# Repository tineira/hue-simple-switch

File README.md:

# hue-simple-switch

Wi‑Fi wall switch for the **Seeed XIAO ESP32-C6**. Calls the Hue Bridge's local Clip v2 API (HTTPS). Not Zigbee.

GPIO channels (closed = pin to GND, `INPUT_PULLUP`):

| id | GPIO | default kind | label |
| --- | --- | --- | --- |
| `boot` | 9 | `momentary` | BOOT |
| `d0` | 0 | `maintained` | D0 |
| `d1` | 1 | `maintained` | D1 |
| `d2` | 2 | `maintained` | D2 |
| `d3` | 21 | none | D3 |
| `d4` | 22 | none | D4 |
| `d5` | 23 | none | D5 |

D3–D5 (GPIO 21–23) are channels since 0.5.0, so one board takes up to six wall switches or buttons on D0–D5, plus BOOT. None of D3–D5 is a strapping pin, and this firmware has no I2C on D4/D5. D6–D10 stay unused (D6 is the chip's serial TX at boot).

Since 0.3.0 the console picks each channel's kind (`maintained` = toggle switch, `momentary` = push button) and sends it in the config's `channels[]`; a pin it does not list does nothing. BOOT is always a push button. The default kinds above apply only to the old config payload (no `channels[]`), from a console that predates channel types; there D3–D5 do nothing, so an unwired pin never acts.

Each channel has recipes per event, derived by the console:

- Toggle switch, flip set (the lever sets on or off; no `flip` in `channels[]`): `on` (lever closes), `off` (lever opens, after the ~400 ms double-click window), `double_click` (opens and closes inside the window; runs `on` when there is no `double_click` recipe).
- Toggle switch, flip toggle (`"flip": "toggle"`, since 0.8.0; each flip toggles, the console sends `toggle` for both `on` and `off`): each flip posts `on` (lever closes) or `off` (lever opens) at once when there is no `double_click` recipe. With one, a flip either way waits ~400 ms: a second flip inside it is `double_click`, otherwise the first flip runs. No `on` fallback. A toggle that turned the lights off restarts the scene list. Boot, a config change or a change of the flip setting never toggles.
- Push button: `short` on release, at once when the channel has no `double_click` recipe; with one, a second press inside ~400 ms is `double_click` and an expired window is `short`. `hold` fires once at ~800 ms while pressed, only when the channel has a `hold` recipe.
- BOOT without a `hold` recipe: a 3 s press re-pairs with the Bridge. With one, the button never re-pairs (USB install only).
- A scene list (`recall_scene` with `targets[]`) cycles from the last scene the channel set (kept in NVS), wraps, skips scenes that answer 404, and starts over at the first scene after an `off` on the channel (in flip toggle mode, after a toggle that turned the target off).

The GPIO runs NVS → Bridge; it doesn't wait for Vercel. Since 0.5.0 the config is stored as one NVS blob per channel, so saving the largest config (seven channels with scene lists) needs only one channel's worth of free space; the first boot after the update converts the older single blob.

Wiring for up to six wall switches or buttons on D0–D5: [`docs/wiring-switches.svg`](docs/wiring-switches.svg). Wire only the inputs you use. The step-by-step build guide (what to buy, wiring one input at a time, what never to connect, and when you need the resistors) is at [hue.tineira.com/how-to](https://hue.tineira.com/how-to?product=simple#wire).

To power the switch from the mains inside a wall box, behind the existing switch, there is a carrier board design (KiCad) and a printable enclosure in [`hardware/`](hardware/README.md). It keeps the same pins and firmware. **Do not build it:** the current board has a known isolation defect, its order files are withdrawn and a revised board is pending. It is an uncertified, experimental mains design: read its safety notes.

> [!WARNING]
> **Safety.** Mains voltage can kill. The designs in this repository are uncertified and some are unproven, and the maintainer is not an electrical engineer. Rules and wire colors differ by country. Read the [Safety notice](https://hue.tineira.com/safety) before you build anything, and never connect any pin of a USB-powered build to anything that is or was on mains. Everything here is provided as is, without warranty, as the licenses say.

**BOOT** (GPIO9) and **RST** (CHIP_PU) are **buttons**, not LEDs. The board has two lights:

The orange LED's alphabet (firmware 0.2.7 and later) is below. Design history: [`docs/archive/specs/led-status.md`](docs/archive/specs/led-status.md).

| Light | Where | Driven by |
| --- | --- | --- |
| Orange (user, GPIO15 `LED_BUILTIN`) | Right side, next to RST | This firmware |
| Red (charging) | Next to the USB-C | The charger hardware; the sketch doesn't touch it |

### Orange LED (firmware)

One pattern at a time, top to bottom. When the step changes, the burst starts from zero. `LOW` on GPIO15 turns the orange on (active low).

| What you see | Meaning |
| --- | --- |
| Solid on | System error: the console task wasn't created, or the console answered 401. The 401 stays solid until a response with a code other than 401, or a new `HUESET token`. Wins even without Wi‑Fi. |
| Continuous blink ~2 Hz (250 ms on / 250 ms off) | No Wi‑Fi STA, or Improv scan. Even with a saved SSID. |
| 2 flashes and a pause | Wi‑Fi ok, no console (URL or token empty, or a `your-…` placeholder). |
| 3 flashes and a pause | Wi‑Fi and console, Hue not paired, or pairing in progress / timed out. Holding BOOT 3 s (re-pair) uses this pattern. |
| 4 flashes and a pause | Wi‑Fi, console and Hue, no recipes. |
| One short flash every ~3 s | Armed: one or more recipes. |

Burst (#2–#4): 100 ms on, 200 ms between flashes, 1400 ms pause. The armed flash lasts 80 ms and repeats every 3 s.

### Red LED (charging, not the sketch)

| What you see | Meaning |
| --- | --- |
| On for ~30 s when USB is plugged in without a battery | USB present; then it turns off. |
| Blinking | LiPo battery connected and charging over USB. |
| Off with USB and battery | Charge complete (or no charge cycle). |

Contract: `hue-switch-console/docs/definitions.md`, `docs/device-api.md` and `docs/usb-protocol.md`.

## Setup

1. Flash and provision from Chrome on [hue.tineira.com](https://hue.tineira.com) → Devices (USB). Improv saves the **2.4 GHz** network and `HUESET` stores the token (`hsw_…`) and url in NVS `console`. None of that is compiled in. For development, copy `config.example.h` to `config.h` (only `SERIAL_DEBUG`); `arduino-cli upload` doesn't erase NVS, so the network and token survive every flash.
2. The XIAO discovers the Bridge (mDNS `_hue._tcp`, NVS, `discovery.meethue.com`) and pairs the Hue key (three orange flashes → Bridge button). IP and key stay in NVS, not in `config.h`.
3. Register: `POST /api/device/register` with `product: "simple"`, MAC, `channels[]` and snapshot (lights/rooms/scenes). Poll: `GET /api/device/config?mac=&rev=&firmware=` at boot, then every `X-Poll-Sec` seconds from the console (clamped 30 s to 1 h; `204` = unchanged, keep NVS), once more right after a new `rev` is saved, and 1 h after a `401`. Without the header (older console): ~1 min without recipes, 1 h with some. With recipes, register (topology) at most hourly.
4. Arduino IDE 2.3.10: open `hue-simple-switch.ino`, board **XIAO_ESP32C6**.
5. Or arduino-cli: `arduino-cli compile --profile xiao-c6 .`

List lamps (diagnostics):

```
curl -k -H "hue-application-key: KEY" https://BRIDGE_IP/clip/v2/resource/light
```

`config.h` is not committed. Product onboarding = the USB installer on hue.tineira.com.

## Release

A push to `main` **is a release**. `.github/workflows/firmware.yml` builds the product image and uploads it to the console (hue.tineira.com) with this version's `CHANGELOG.md` entry as release notes. The console's USB installer then offers that build to every Simple plugged in over USB, and since 0.6.0 the owner can send it over Wi-Fi from the Switches page (below). The workflow also keeps the `usb-installer` GitHub Release as a download link. Pushes that change only docs or the board design (`*.md`, `docs/`, `hardware/`) do not run it, except `CHANGELOG.md`, which re-sends the notes. To skip any other push, put `[skip ci]` in its commit message.

- `FIRMWARE_VERSION` in `console.h` is the version the console shows. Bump it for any change a board should pick up, and add its entry to `CHANGELOG.md` in the same commit. A push without a bump re-sends the notes only (`409 version_exists` warning).
- `THIRD_PARTY.json` lists the open-source components linked into the image (the core, ESP-IDF, and every library pinned in `sketch.yaml`), with version, SPDX license and a link to the license at that version. CI sends it as the release `credits` for the console's Credits page, and fails if any `platform:` or `libraries:` entry in `sketch.yaml` is missing from it or has a different version (`scripts/check-credits.py`, run on every pull request too). Update it in the same commit as any core or library bump.
- Update over Wi-Fi (0.6.0+; wire: console `docs/device-api.md`, design history: console `docs/archive/specs/ota.md`): when the owner presses Update, the next poll's `200` carries `ota` (version, path, sha256, size). After the poll's connection is closed, the console task downloads `firmware.bin` from the console URL in NVS, writes it to the inactive app slot while hashing it, checks length and sha256, and restarts into it. It waits for the next poll while an input is pressed or a Hue call is queued or running. The new image confirms itself after its first `200`/`204` poll; a restart before that makes the bootloader go back to the old one, which reports `ota_error=boot`. A failure is reported once as `ota_error` and retried at most hourly (a download cut off by a power cut or restart counts, reported as `size` at the next boot, since 0.6.1) (`size`/`sha` from a bad image: not until reboot). NVS is never erased. Boards before 0.6.0 need one USB update first.
- Image layout and offsets: [`docs/firmware-artifacts.md`](docs/firmware-artifacts.md).
- The pipeline needs the `FIRMWARE_UPLOAD_TOKEN` secret in this repo. Setup and troubleshooting: the console repo's `README.md`, "Firmware release pipeline".

### Build and upload from a fork

A fork builds the same image on every push to its `main`, and can upload it to your own console instead of hue.tineira.com (self-hosting: the console repo's `docs/self-hosting.md`).

- **Build only (default).** With no `FIRMWARE_UPLOAD_TOKEN` secret, the workflow builds, skips the upload with a notice and stays green. The four installer parts are in the run's `usb-installer-simple` artifact and in the fork's `usb-installer` GitHub Release.
- **Upload to your console.** In the fork's **Settings → Secrets and variables → Actions**:
  1. Add the repository **variable** `CONSOLE_UPLOAD_URL` with your console's origin, for example `https://hue.example.com` (no path, no trailing slash). Without it, the upload goes to `https://hue.tineira.com`, which rejects a fork's token.
  2. Add the repository **secret** `FIRMWARE_UPLOAD_TOKEN` with the value of `FIRMWARE_UPLOAD_TOKEN` on your console.
  3. Push to `main` (or run the workflow by hand). The release waits in your console's `/admin` until you make it current; Setup then flashes it.
- Bump `FIRMWARE_VERSION` in `console.h` and add its `CHANGELOG.md` entry for each build you want boards to get, as above: your console keeps the first bins it received for a version.

## Contributing

See [`CONTRIBUTING.md`](CONTRIBUTING.md). Bugs and ideas go in GitHub issues.

## Sponsor

The console and the switch firmwares are free and stay that way. If they are useful
to you, you can [sponsor the project on GitHub](https://github.com/sponsors/tineira).
Sponsorship helps pay for development and does not unlock anything.

## License

Copyright (c) 2026 Tomas Neira and contributors. [MIT](LICENSE), except the
carrier board and enclosure designs in `hardware/`, which are
[CERN-OHL-P-2.0](hardware/LICENSE) (see [`hardware/README.md`](hardware/README.md)).

The image also links open-source components under their own licenses, listed in
[`THIRD_PARTY.json`](THIRD_PARTY.json). The Arduino-ESP32 core is LGPL-2.1-or-later:
because this firmware's source is public, you can rebuild it against a modified core.

The console this firmware talks to, [`hue-switch-console`](https://github.com/tineira/hue-switch-console),
is AGPL-3.0; it also holds the device contract (`docs/device-api.md`).

Not affiliated with or endorsed by Signify. Philips Hue is a trademark of Signify.

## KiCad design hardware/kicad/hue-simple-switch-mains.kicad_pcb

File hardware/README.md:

# Mains carrier board and enclosure

A small board that puts the XIAO ESP32-C6 and its own power supply inside a wall
electrical box, powered from the mains, reading the existing wall switches or
buttons on D0 to D5. Firmware, pin map and console contract are unchanged: this
is the same `hue-simple-switch`, with a different way to power and wire it.

> [!WARNING]
> **Mains voltage can kill.** This is an uncertified design, produced with AI
> assistance and checked only by the design-rule tools listed below. It has not
> been tested by a lab and carries no approval mark (CE, UL, SEC or other).
> Have a qualified electrician install it. Switch the circuit off at the
> breaker before opening the box, and check it is dead with a tester.
> Build and install it at your own risk.
>
> - **Known isolation defect: do not build this board.** GND copper sits
>   1.5 mm from mains copper on both layers, not the intended 6 mm. The order
>   files are withdrawn and a revised board is pending.
> - **Revised board, untested: do not build it yet.** [`v2-fit/`](v2-fit/REPORT.md)
>   holds the revised design and its order files. Prototypes were ordered on
>   2026-11-01 and none has been assembled or tested.
> - **Status: experimental.** The first boards came back from JLCPCB in
>   October 2026. One passed the checks in [TESTING.md](TESTING.md) and ran
>   on mains with the XIAO, showing in the console. That board later failed.
>   The cause is not proven. None has been installed in a wall.
> - The maintainer is not an electrical engineer. This is a hobby design.
> - Rules and wire colors differ by country and with the age of the wiring.
>   Identify every conductor by testing it, never by its color. In some
>   countries only a licensed electrician may change fixed wiring.
> - An uncertified device in your home's wiring may affect your home insurance.
>
> Read the full [Safety notice](https://hue.tineira.com/safety) before you order
> anything.

The XIAO has no 3D model in these renders. It sits flat on the top side, USB-C
at the left edge.

## What is on the board

| Part | What it does |
| --- | --- |
| J1, 2-way 5.08 mm screw terminal | Mains in: L and N (up to 2.5 mm²) |
| F1, T500 mA TR5 fuse | Protects the wiring if the module or varistor fails |
| RV1, TDK SIOV CU3225 275 VAC SMD varistor (8.0 × 6.3 × 4.5 mm) | Clamps mains surges at the module input, after the fuse |
| PS1, Hi-Link HLK-PM01 | Certified, sealed, isolated 100-240 V AC to 5 V DC module (3 kV AC isolation) |
| D1, SS34 Schottky diode | Feeds the XIAO's 5V pin; stops a USB cable from powering the module backwards |
| U1, XIAO ESP32-C6 | Soldered flat by its edge pads |
| J2 + J3, 3.5 mm screw terminals | Wall switch inputs **D0 D1 D2 D3** and **D4 D5 GND**. Low voltage (3.3 V) only |
| R1-R6, R11-R16, C11-C16 | Each input: 10 kΩ pull-up at the pin, 1 kΩ in series, 10 nF at the terminal |

The pin map is the firmware's (see the repo [README](../README.md) and
[`docs/wiring-switches.svg`](../docs/wiring-switches.svg)): D0 to D5 are GPIO 0, 1,
2, 21, 22 and 23. A closed switch pulls its pin to GND. BOOT (hold 3 s to re-pair
with the Hue Bridge) and RESET are the XIAO's own buttons, reachable through the
window in the lid.

Isolation: the design target is at least **6 mm** of clearance and creepage from
everything connected to L or N to everything else. **The current board does not
meet it:** the GND pour is 1.5 mm from mains copper on both layers, and DRC did
not report this. A routed slot under the power module separates its AC pins from
the XIAO. The HLK-PM01 is the only intended link between the two sides.

The console's build guide has a short "can I use it?" check, a before-and-after wiring drawing and the installation order to show your electrician: [hue.tineira.com/how-to](https://hue.tineira.com/how-to?product=simple#in-wall).

Schematic: [`fab/hue-simple-switch-mains-schematic.pdf`](fab/hue-simple-switch-mains-schematic.pdf).

## Does it fit my box?

Enclosure outside: **46 × 56 mm, 26 mm tall** (a Ø56 mm disc with two sides cut
flat at 46 mm). It sits **behind the switch mechanism** in the same box, so the
box needs about 26 mm of free depth behind the mechanism.

| Box | Interior (typical) | Behind a mechanism |
| --- | --- | --- |
| EU round, Ø60 mm (DIN 49073) | Ø60 × 40 mm, or 60 to 65 mm deep | Deep box (≥ 60 mm) only. A standard 40 mm box is too shallow |
| US single gang | about 51 × 76 mm, 2.5 to 3.5 in deep | Yes, in most boxes |
| UK 86 × 86 (BS 4662) | 75 × 75 mm, 25, 35 or 47 mm deep | 47 mm box only |
| Chile, rectangular for Italian-style plates | about 50 × 95 mm, 40 to 50 mm deep | No room behind a mechanism, but it fits **beside** a 1-module mechanism, in the space of two blank modules (56 mm along the box) |

The Chilean dimensions come from retail listings, not a standard. Measure your
box: the width across the flats (46 mm) and the depth are what matter. In a
metal box, Wi-Fi range drops a lot; plastic boxes are better.

## Before you install: requirements

- **A neutral wire in the box.** The power module needs L and N. Many switch
  boxes (in Chile, and in older US and European homes) only have the switched
  live and the live feed, with no neutral. Without a neutral this board cannot
  be used. There is no safe no-neutral version for this design.
- **The Hue bulbs must be powered all the time.** The wall switch no longer
  switches the lamp; the lamp's live is joined straight through (as the
  existing Hue setup already requires).
- **The switch wires must be completely disconnected from the mains.** The
  wires that run from the box to each switch or button were mains wires. After
  the conversion they carry only 3.3 V from J2/J3. Every one of them must be
  disconnected from L, N and the lamp at both ends, and must go only to the
  switch and to J2/J3. If any of them still touches mains anywhere, the XIAO,
  and anyone touching its USB port, will be at mains voltage. An electrician
  must check this.

## Order assembled boards (JLCPCB)

> [!CAUTION]
> **Do not order this board.** The Gerbers, BOM and placement files were
> withdrawn because of the isolation defect described under [What is on the
> board](#what-is-on-the-board). A revised board is pending. Do not generate
> new order files from `kicad/`: they would carry the same defect. The revised
> board in [`v2-fit/`](v2-fit/REPORT.md) is untested: its order files are there
> for the record, not for you to order yet.

Boards already made from the withdrawn files carry the same defect. Do not put
them on mains.

## Check the board

Before the XIAO goes on and before the board sees mains, check it with a
multimeter: continuity on the mains side, isolation between mains and the
low-voltage side, the input resistors, and a first power-up through a lamp in
series. The steps, the expected readings and the readings from the first board
are in [TESTING.md](TESTING.md). Passing them does not show that a board is safe:
a multimeter did not find the 1.5 mm gap.

## Solder the XIAO

1. **Flash and set up the XIAO over USB before you solder it** (next section).
   It is easier on its own, and afterwards the board should not be on USB at the
   same time as mains.
2. Solder it flat on the top side, USB-C over the left board edge. Solder all 14
   edge pads (only D0-D5, 5V, GND and 3V3 are used; the others hold it in
   place). Do not let solder bridge to the bare pads under the XIAO; the board
   has no copper under it.
3. Inspect the mains side with a magnifier: no solder balls, splashes or flux
   bridges between L, N and anything else. Trim the through-hole leads on the
   top side to 1.5 mm or less so they do not touch the lid.

## First setup (USB, never on mains)

Do this with the board **not connected to mains** (before soldering the XIAO,
or with J1 disconnected):

1. Flash and provision it over USB-C like any other hue-simple-switch: Chrome
   on [hue.tineira.com](https://hue.tineira.com) → Devices (see the main
   [README](../README.md)). Then pair the Hue Bridge.
2. Unplug USB.

After installation, updates come over Wi-Fi (firmware 0.6.0 and newer), so USB
is never needed in the wall.

> [!CAUTION]
> **Never connect a USB cable while the board is connected to mains.** The power
> module is isolated, but a fault, a wrongly wired switch line or a damaged
> module would put mains on the USB cable and on your computer.

## Wire it

```text
 mains L (permanent live) ── J1 L          Hue lamps: live joined straight through,
 mains N ─────────────────── J1 N          not through the switch any more

 switch 1 ── J2 D0     switch 4 ── J2 D3
 switch 2 ── J2 D1     switch 5 ── J3 D4
 switch 3 ── J2 D2     switch 6 ── J3 D5
 other terminal of every switch, joined ── J3 GND
```

- Use only the inputs you need, and set each one up in the console (toggle
  switch or push button).
- The common return of all switches goes to the single GND terminal: join them
  first with a lever connector (for example WAGO 221) and bring one wire to J3.
- The screw terminals take up to 2.5 mm² (J1) and about 1 mm² (J2/J3). For
  1.5 mm² solid building wire on J2/J3, join a short 0.5-0.75 mm² flexible
  pigtail with a lever connector.
- Keep the switch wires on the low-voltage side of the enclosure (wire holes on
  the long straight side next to D0-D3, and the curved end next to D4-GND). The
  L/N holes are the two larger ones at the other end of the straight side.
- Earth (PE): the module does not need it. Connect the box's earth wires to each
  other as before, not to this board.

## Print the enclosure

- [`enclosure/enclosure-base.stl`](enclosure/enclosure-base.stl) and
  [`enclosure/enclosure-lid.stl`](enclosure/enclosure-lid.stl), both already
  oriented flat side down. No supports.
- Plastic: **not PLA** (it softens and creeps in a warm wall box). Use PETG, ASA
  or PC; ideally a flame-retardant (UL 94 V-0) grade. 0.2 mm layers, 3 walls,
  100 % infill for the floor.
- The board rests on posts in the base (power module down); the lid clicks over
  it and its posts hold the board down. The terminal screws are reached through
  the slots in the base floor. Tighten the wires before closing the lid, and
  put a strip of Kapton or electrical tape over the floor slots before the
  module goes into the wall.
- Source: [`enclosure/enclosure.scad`](enclosure/enclosure.scad) (OpenSCAD,
  parametric: wall, clearances, heights, hole sizes). The board as a 3D model is
  in `enclosure/hue-simple-switch-mains-board.step` for checking the fit in a
  CAD tool.

Layout of the enclosure, seen from the lid (XIAO side):

```text
            ┌─── round end ───┐
           /  MAINS: F1, RV1   \
          │  (module AC pins)   │  J1: L, N  ◄── two Ø3.6 wire holes
  USB-C ◄─┤  XIAO     ··········├─ J2: D0-D3 ◄── four Ø3.0 wire holes
 + window │  (over the module)  │
           \   J3: D4 D5 GND   /
            └──── ▼ three Ø3.0 wire holes
```

## Regenerate the files

Everything in `kicad/`, `fab/`, `images/` and the STLs is generated from
[`scripts/design.py`](scripts/design.py) (parts, nets),
[`scripts/layout.py`](scripts/layout.py) (placement, copper) and
[`scripts/footprints.py`](scripts/footprints.py) (footprints and height models
for the power module, varistor and terminal blocks, drawn from each
manufacturer's datasheet; the numbers are quoted in the file). Edit those, not
the KiCad files, then run with KiCad 10's own Python:

```bash
"$LOCALAPPDATA/Programs/KiCad/10.0/bin/python.exe" hardware/scripts/build_all.py
```

It writes the schematic and runs ERC, builds the PCB, refills the copper pours
and runs DRC with schematic parity (it stops on any error), then exports the
Gerber zip, BOM, CPL, PDFs, STEP, renders, builds the 3-board panel
([`scripts/build_panel.py`](scripts/build_panel.py)) and checks it with DRC
too, exports its JLCPCB files into `fab/jlcpcb/`, and, when OpenSCAD is
installed, the STLs. Reports: `fab/erc.rpt`, `fab/drc.rpt` (the remaining warnings are
silkscreen clipped at the board edge, which the fab trims anyway). The 6 mm
rules are in `kicad/hue-simple-switch-mains.kicad_dru`. The rules that the
withdrawn files were built with did not apply to copper pours, so a clean DRC
from them says nothing about the GND gap. The Gerbers, BOMs and CPLs are
gitignored until the revised board is released.

You can also open `kicad/hue-simple-switch-mains.kicad_pro` in KiCad 10 to look
around; changes made there are lost at the next regeneration.

## Credits and licenses

- XIAO ESP32-C6 footprint: from Seeed Studio's
  [OPL_Kicad_Library](https://github.com/Seeed-Studio/OPL_Kicad_Library)
  (CC BY-SA 4.0), reduced to the 14 edge pads in `kicad/lib/XIAO.pretty`.
- Other symbols, footprints and 3D models: the KiCad libraries (CC BY-SA 4.0
  with the KiCad libraries exception).
- The board design and enclosure (`kicad/`, `fab/`, `enclosure/`, `images/`)
  are [CERN-OHL-P-2.0](LICENSE), a permissive open hardware license with a
  disclaimer written for physical hardware. The generator scripts in `scripts/`
  are software and stay MIT, like the rest of this repository.

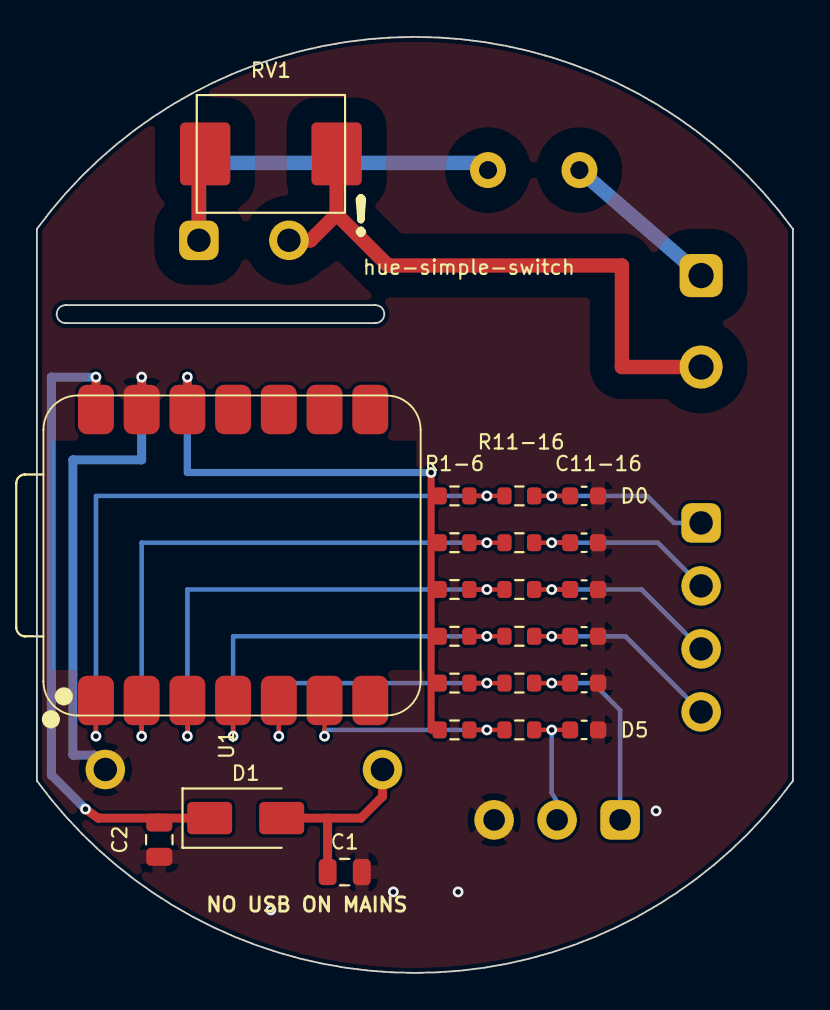
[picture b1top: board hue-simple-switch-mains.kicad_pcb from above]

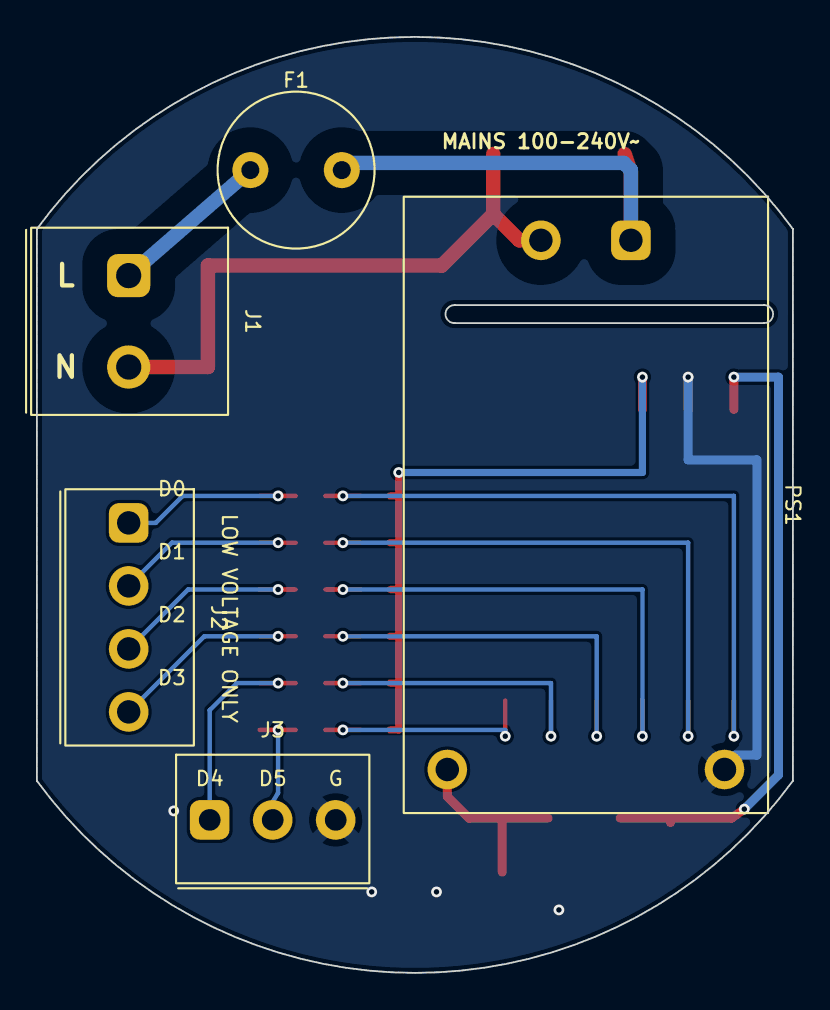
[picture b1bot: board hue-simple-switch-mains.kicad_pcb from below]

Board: 2 copper layers, 42.0 x 52.0 mm, 28 parts (5 on the bottom side), 19 nets.

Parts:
C1, C2: 22uF 25V; C_0805_2012Metric
C11, C12, C13, C14, C15, C16: 10nF; C_0603_1608Metric
D1: SS34; D_SMA
F1: T500mA 250V; Fuse_Littelfuse_372_D8.50mm
J1: MAINS L/N; TerminalBlock_Kefa_KF128-5.08_1x02
J2: D0 D1 D2 D3; TerminalBlock_Xinlaiya_XY350V-3.5_1x04
J3: D4 D5 GND; TerminalBlock_Kefa_KF350-3.5_1x03
PS1: HLK-PM01; HiLink_HLK-PM01
R1, R2, R3, R4, R5, R6: 10k; R_0603_1608Metric
R11, R12, R13, R14, R15, R16: 1k; R_0603_1608Metric
RV1: 275VAC; RV_TDK_SIOV_CU3225
U1: XIAO ESP32-C6; XIAO-ESP32-C6-SMD-EdgePads

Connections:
+3V3: R1.1, R2.1, R3.1, R4.1, R5.1, R6.1, U1.12
+5V: C2.1, D1.1, U1.14
+5V_PSU: C1.1, D1.2, PS1.4
AC_L: F1.2, PS1.1, RV1.1
AC_L_IN: F1.1, J1.1
AC_N: J1.2, PS1.2, RV1.2
D0: R1.2, R11.2, U1.1
D1: R2.2, R12.2, U1.2
D2: R3.2, R13.2, U1.3
D3: R4.2, R14.2, U1.4
D4: R5.2, R15.2, U1.5
D5: R6.2, R16.2, U1.6
GND: C1.2, C2.2, C11.2, C12.2, C13.2, C14.2, C15.2, C16.2, J3.3, PS1.3, U1.13
IN_D0: C11.1, J2.1, R11.1
IN_D1: C12.1, J2.2, R12.1
IN_D2: C13.1, J2.3, R13.1
IN_D3: C14.1, J2.4, R14.1
IN_D4: C15.1, J3.1, R15.1
IN_D5: C16.1, J3.2, R16.1

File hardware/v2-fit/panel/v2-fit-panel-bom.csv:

Comment,Designator,Footprint,LCSC Part #
22uF 25V,"C1_1,C1_2,C1_3,C2_1,C2_2,C2_3",C_0805_2012Metric,C45783
10nF,"C11_1,C11_2,C11_3,C12_1,C12_2,C12_3,C13_1,C13_2,C13_3,C14_1,C14_2,C14_3,C15_1,C15_2,C15_3,C16_1,C16_2,C16_3",C_0603_1608Metric,C57112
SS34,"D1_1,D1_2,D1_3",D_SMA,C8678
500mA 600V Slo-Blo,"F1_1,F1_2,F1_3",Fuse_Littelfuse_461,C206981
JST B7B-PH-SM4-TB,"J2_1,J2_2,J2_3",JST_PH_B7B-PH-SM4-TB_1x07-1MP_P2.00mm_Vertical,C495700
1k,"R11_1,R11_2,R11_3,R12_1,R12_2,R12_3,R13_1,R13_2,R13_3,R14_1,R14_2,R14_3,R15_1,R15_2,R15_3,R16_1,R16_2,R16_3",R_0603_1608Metric,C21190
275VAC,"RV1_1,RV1_2,RV1_3",RV_TDK_SIOV_CU3225,C600605
Socket 1x6 2.54 H8.5 YQ,"U1A_1,U1A_2,U1A_3",XIAO_socket_6+2,C46635842
Socket 1x2 2.54 H8.5 YQ,"U1B_1,U1B_2,U1B_3",XIAO_socket_6+2,C46635838

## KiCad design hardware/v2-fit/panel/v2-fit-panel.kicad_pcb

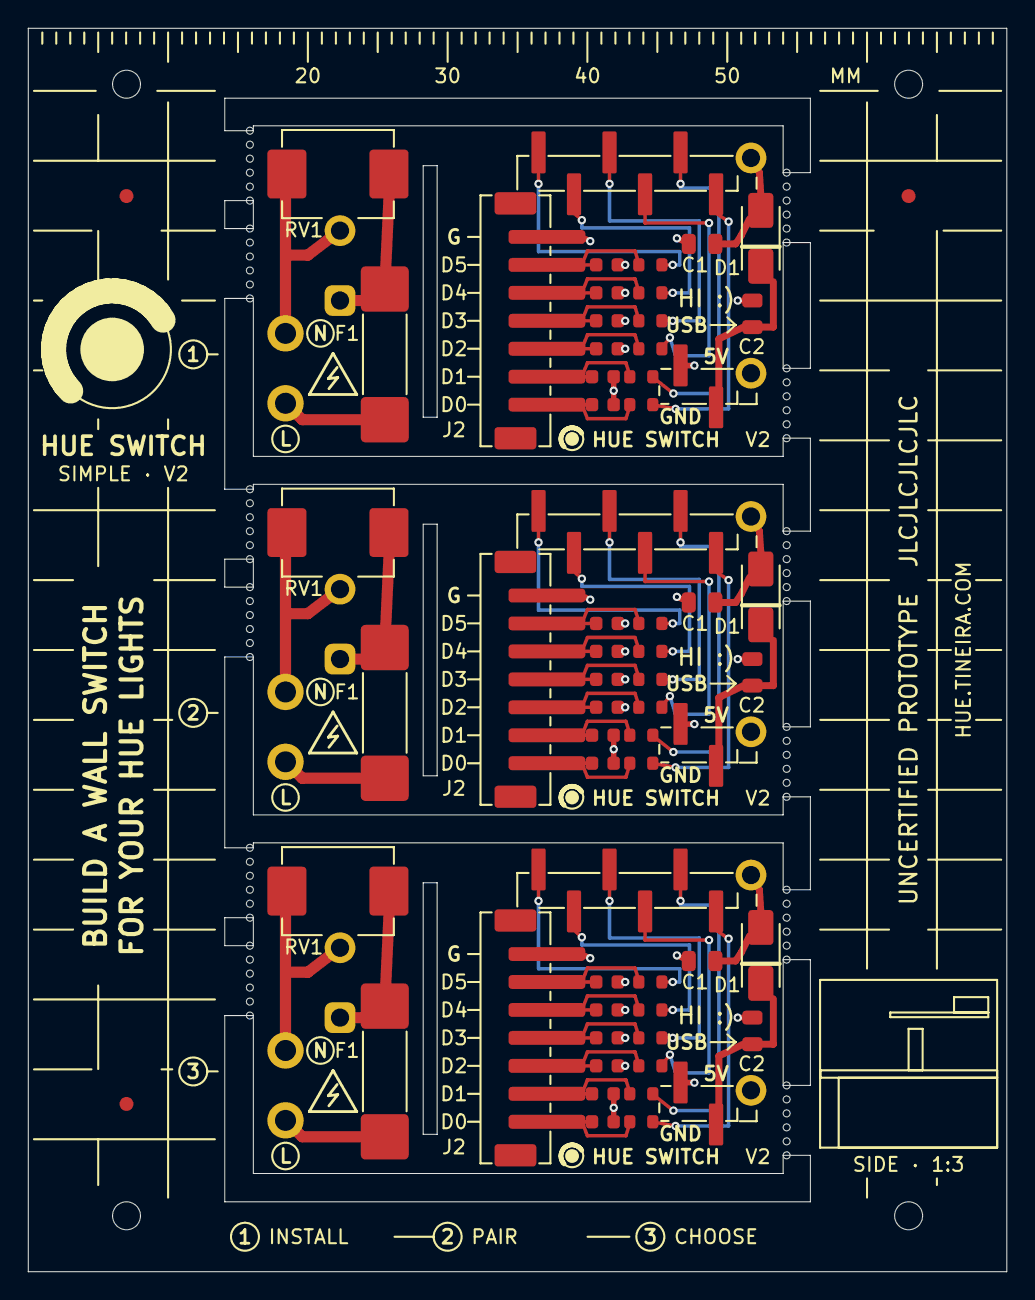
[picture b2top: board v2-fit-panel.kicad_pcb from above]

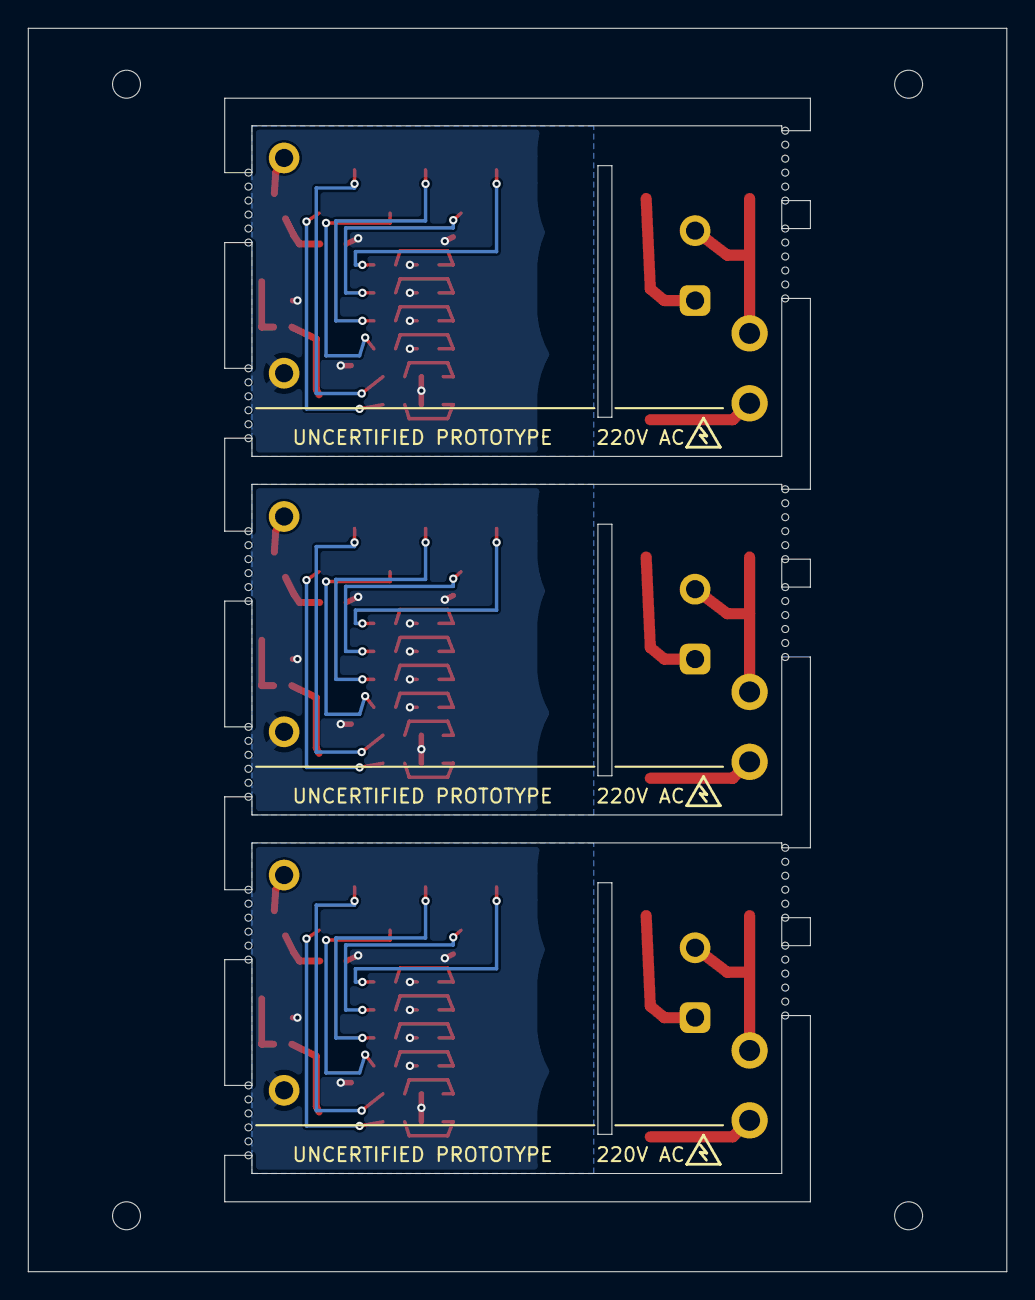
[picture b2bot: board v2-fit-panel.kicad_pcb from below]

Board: 2 copper layers, 70.0 x 88.9 mm, 145 parts (3 on the bottom side), 54 nets.

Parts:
C1_1, C1_2, C1_3, C2_1, C2_2, C2_3: 22uF 25V; C_0805_2012Metric
C11_1, C11_2, C11_3, C12_1, C12_2, C12_3, C13_1, C13_2, C13_3, C14_1, C14_2, C14_3, C15_1, C15_2, C15_3, C16_1, C16_2, C16_3: 10nF; C_0603_1608Metric
D1_1, D1_2, D1_3: SS34; D_SMA
F1_1, F1_2, F1_3: T500mA 600V; Fuse_Littelfuse_461
FID1, FID2, FID3: Fiducial_1mm_Mask2mm
J2_1, J2_2, J2_3: D0-D5 GND; JST_PH_B7B-PH-SM4-TB_1x07-1MP_P2.00mm_Vertical
MB1, MB2, MB3, MB4, MB5, MB6, MB7, MB8, MB9, MB10, MB11, MB12, MB13, MB14, MB15, MB16, MB17, MB18, MB19, MB20, MB21, MB22, MB23, MB24, MB25, MB26, MB27, MB28, MB29, MB30, MB31, MB32, MB33, MB34, MB35, MB36, MB37, MB38, MB39, MB40, MB41, MB42, MB43, MB44, MB45, MB46, MB47, MB48, MB49, MB50, MB51, MB52, MB53, MB54, MB55, MB56, MB57, MB58, MB59, MB60, MB61, MB62, MB63, MB64, MB65, MB66, MB67, MB68, MB69, MB70, MB71, MB72: (no value)
PS1_1, PS1_2, PS1_3: HLK-PM01; HiLink_HLK-PM01_lifted
R11_1, R11_2, R11_3, R12_1, R12_2, R12_3, R13_1, R13_2, R13_3, R14_1, R14_2, R14_3, R15_1, R15_2, R15_3, R16_1, R16_2, R16_3: 1k; R_0603_1608Metric
RV1_1, RV1_2, RV1_3: 275VAC; RV_TDK_SIOV_CU3225
TH1, TH2, TH3, TH4: (no value)
U1_1, U1_2, U1_3: XIAO ESP32-C6 socket; XIAO_socket_6+2
WL_1, WL_2, WL_3: L wire; Wire_0.75mm2
WN_1, WN_2, WN_3: N wire; Wire_0.75mm2

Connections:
+5V_PSU_b1: C1_1.1, D1_1.2, PS1_1.4
+5V_PSU_b2: C1_2.1, D1_2.2, PS1_2.4
+5V_PSU_b3: C1_3.1, D1_3.2, PS1_3.4
+5V_b1: C2_1.1, D1_1.1, U1_1.5V
+5V_b2: C2_2.1, D1_2.1, U1_2.5V
+5V_b3: C2_3.1, D1_3.1, U1_3.5V
AC_L_IN_b1: F1_1.1, WL_1.1
AC_L_IN_b2: F1_2.1, WL_2.1
AC_L_IN_b3: F1_3.1, WL_3.1
AC_L_b1: F1_1.2, PS1_1.1, RV1_1.1
AC_L_b2: F1_2.2, PS1_2.1, RV1_2.1
AC_L_b3: F1_3.2, PS1_3.1, RV1_3.1
AC_N_b1: PS1_1.2, RV1_1.2, WN_1.1
AC_N_b2: PS1_2.2, RV1_2.2, WN_2.1
AC_N_b3: PS1_3.2, RV1_3.2, WN_3.1
D0_b1: R11_1.2, U1_1.D0
D0_b2: R11_2.2, U1_2.D0
D0_b3: R11_3.2, U1_3.D0
D1_b1: R12_1.2, U1_1.D1
D1_b2: R12_2.2, U1_2.D1
D1_b3: R12_3.2, U1_3.D1
D2_b1: R13_1.2, U1_1.D2
D2_b2: R13_2.2, U1_2.D2
D2_b3: R13_3.2, U1_3.D2
D3_b1: R14_1.2, U1_1.D3
D3_b2: R14_2.2, U1_2.D3
D3_b3: R14_3.2, U1_3.D3
D4_b1: R15_1.2, U1_1.D4
D4_b2: R15_2.2, U1_2.D4
D4_b3: R15_3.2, U1_3.D4
D5_b1: R16_1.2, U1_1.D5
D5_b2: R16_2.2, U1_2.D5
D5_b3: R16_3.2, U1_3.D5
GND_b1: C1_1.2, C2_1.2, C11_1.2, C12_1.2, C13_1.2, C14_1.2, C15_1.2, C16_1.2, J2_1.7, PS1_1.3, U1_1.GND
GND_b2: C1_2.2, C2_2.2, C11_2.2, C12_2.2, C13_2.2, C14_2.2, C15_2.2, C16_2.2, J2_2.7, PS1_2.3, U1_2.GND
GND_b3: C1_3.2, C2_3.2, C11_3.2, C12_3.2, C13_3.2, C14_3.2, C15_3.2, C16_3.2, J2_3.7, PS1_3.3, U1_3.GND
IN_D0_b1: C11_1.1, J2_1.1, R11_1.1
IN_D0_b2: C11_2.1, J2_2.1, R11_2.1
IN_D0_b3: C11_3.1, J2_3.1, R11_3.1
IN_D1_b1: C12_1.1, J2_1.2, R12_1.1
IN_D1_b2: C12_2.1, J2_2.2, R12_2.1
IN_D1_b3: C12_3.1, J2_3.2, R12_3.1
IN_D2_b1: C13_1.1, J2_1.3, R13_1.1
IN_D2_b2: C13_2.1, J2_2.3, R13_2.1
IN_D2_b3: C13_3.1, J2_3.3, R13_3.1
IN_D3_b1: C14_1.1, J2_1.4, R14_1.1
IN_D3_b2: C14_2.1, J2_2.4, R14_2.1
IN_D3_b3: C14_3.1, J2_3.4, R14_3.1
IN_D4_b1: C15_1.1, J2_1.5, R15_1.1
IN_D4_b2: C15_2.1, J2_2.5, R15_2.1
IN_D4_b3: C15_3.1, J2_3.5, R15_3.1
IN_D5_b1: C16_1.1, J2_1.6, R16_1.1
IN_D5_b2: C16_2.1, J2_2.6, R16_2.1
IN_D5_b3: C16_3.1, J2_3.6, R16_3.1

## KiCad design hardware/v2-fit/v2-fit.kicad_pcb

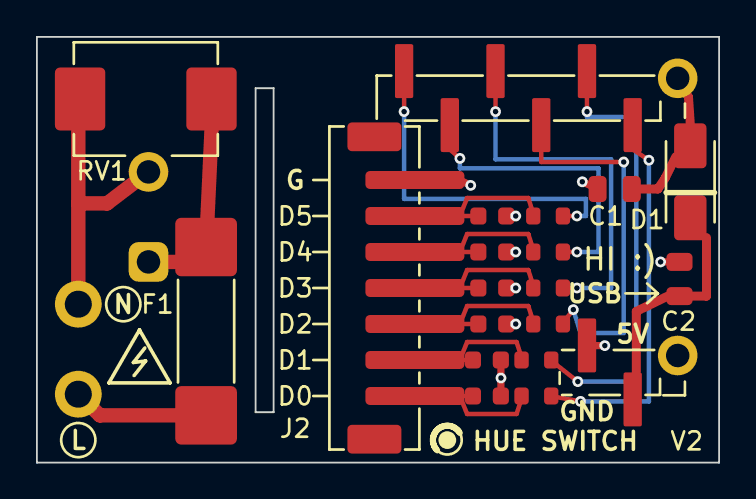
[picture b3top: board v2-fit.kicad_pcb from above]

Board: 2 copper layers, 37.9 x 23.6 mm, 24 parts (1 on the bottom side), 18 nets.

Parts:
BOX1: Box interior; box_38x24x36
C1, C2: 22uF 25V; C_0805_2012Metric
C11, C12, C13, C14, C15, C16: 10nF; C_0603_1608Metric
D1: SS34; D_SMA
F1: T500mA 600V; Fuse_Littelfuse_461
J2: D0-D5 GND; JST_PH_B7B-PH-SM4-TB_1x07-1MP_P2.00mm_Vertical
PS1: HLK-PM01; HiLink_HLK-PM01_lifted
R11, R12, R13, R14, R15, R16: 1k; R_0603_1608Metric
RV1: 275VAC; RV_TDK_SIOV_CU3225
U1: XIAO ESP32-C6 socket; XIAO_socket_6+2
WL: L wire; Wire_0.75mm2
WN: N wire; Wire_0.75mm2
XM1: XIAO seated; XIAO_seated

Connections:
+5V: C2.1, D1.1, U1.5V
+5V_PSU: C1.1, D1.2, PS1.4
AC_L: F1.2, PS1.1, RV1.1
AC_L_IN: F1.1, WL.1
AC_N: PS1.2, RV1.2, WN.1
D0: R11.2, U1.D0
D1: R12.2, U1.D1
D2: R13.2, U1.D2
D3: R14.2, U1.D3
D4: R15.2, U1.D4
D5: R16.2, U1.D5
GND: C1.2, C2.2, C11.2, C12.2, C13.2, C14.2, C15.2, C16.2, J2.7, PS1.3, U1.GND
IN_D0: C11.1, J2.1, R11.1
IN_D1: C12.1, J2.2, R12.1
IN_D2: C13.1, J2.3, R13.1
IN_D3: C14.1, J2.4, R14.1
IN_D4: C15.1, J2.5, R15.1
IN_D5: C16.1, J2.6, R16.1

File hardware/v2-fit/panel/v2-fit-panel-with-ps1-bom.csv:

Comment,Designator,Footprint,LCSC Part #
22uF 25V,"C1_1,C1_2,C1_3,C2_1,C2_2,C2_3",C_0805_2012Metric,C45783
10nF,"C11_1,C11_2,C11_3,C12_1,C12_2,C12_3,C13_1,C13_2,C13_3,C14_1,C14_2,C14_3,C15_1,C15_2,C15_3,C16_1,C16_2,C16_3",C_0603_1608Metric,C57112
SS34,"D1_1,D1_2,D1_3",D_SMA,C8678
500mA 600V Slo-Blo,"F1_1,F1_2,F1_3",Fuse_Littelfuse_461,C206981
JST B7B-PH-SM4-TB,"J2_1,J2_2,J2_3",JST_PH_B7B-PH-SM4-TB_1x07-1MP_P2.00mm_Vertical,C495700
HLK-PM01,"PS1_1,PS1_2,PS1_3",PWRM-TH_HLK-PM01,C209903
1k,"R11_1,R11_2,R11_3,R12_1,R12_2,R12_3,R13_1,R13_2,R13_3,R14_1,R14_2,R14_3,R15_1,R15_2,R15_3,R16_1,R16_2,R16_3",R_0603_1608Metric,C21190
275VAC,"RV1_1,RV1_2,RV1_3",RV_TDK_SIOV_CU3225,C600605
Socket 1x6 2.54 H8.5 YQ,"U1A_1,U1A_2,U1A_3",XIAO_socket_6+2,C46635842
Socket 1x2 2.54 H8.5 YQ,"U1B_1,U1B_2,U1B_3",XIAO_socket_6+2,C46635838

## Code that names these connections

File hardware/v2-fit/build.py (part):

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    outline(board)

    fps = {}
    # PS1: pin 1 (AC_L) at the lower of the two AC pins, AC end on the mains side
    l_pin = (PS1_C[0] - 14.7, PS1_C[1] + 2.5)
    fps["PS1"] = place(board, nets, "PS1", "HiLink_HLK-PM01_lifted", l_pin, 0, "bottom",
                       {"1": "AC_L", "2": "AC_N", "3": "GND", "4": "+5V_PSU"}, "HLK-PM01")
    fps["WL"] = place(board, nets, "WL", "Wire_0.75mm2", WIRE_L, pins={"1": "AC_L_IN"}, value="L wire")
    fps["WL"].Reference().SetVisible(False)
    fps["WN"] = place(board, nets, "WN", "Wire_0.75mm2", WIRE_N, pins={"1": "AC_N"}, value="N wire")
    fps["WN"].Reference().SetVisible(False)
    jpins = {str(i + 1): "IN_D%d" % i for i in range(6)}
    jpins["7"] = "GND"
    fps["J2"] = place(board, nets, "J2", "JST_PH_B7B-PH-SM4-TB_1x07-1MP_P2.00mm_Vertical", TERM_AT, 90,
                      pins=jpins, value="D0-D5 GND")
    fps["F1"] = place(board, nets, "F1", "Fuse_Littelfuse_461", F1_C, 90,
                      pins={"1": "AC_L_IN", "2": "AC_L"}, value="T500mA 600V")
    fps["RV1"] = place(board, nets, "RV1", "RV_TDK_SIOV_CU3225", RV_C, 180,
                       pins={"1": "AC_L", "2": "AC_N"}, value="275VAC")
    fps["U1"] = place(board, nets, "U1", "XIAO_socket_6+2", X_C,
                      pins={k: v for k, v in SOCKET_NET.items() if v}, value="XIAO ESP32-C6 socket")
    # the model is drawn in board axes: USB toward +x, pins at the socket positions
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    T("AC_L", [f_out, (f_out[0] - 1.0, l_p[1]), l_p], F)
    T("AC_L", [f_out, (rv_l[0], rv_l[1] + 1.75)], F)
    T("AC_N", [WIRE_N, (WIRE_N[0], rv_n[1] + 1.75)], F)
    T("AC_N", [(WIRE_N[0], -2.6), (-15.0, -2.6), n_pin], F)

    # ------------------------------------------------------------ low voltage
    # Inputs on top: J2 -> C, and past C to R in the gap above the row. Signals drop to the
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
